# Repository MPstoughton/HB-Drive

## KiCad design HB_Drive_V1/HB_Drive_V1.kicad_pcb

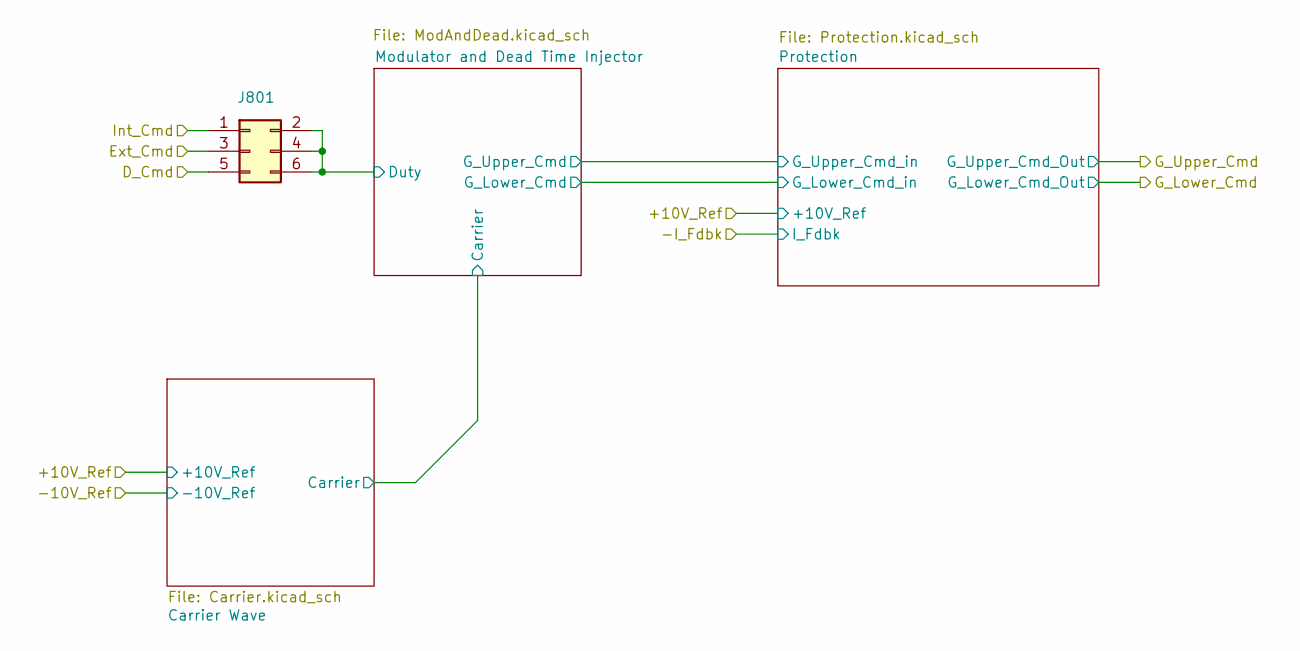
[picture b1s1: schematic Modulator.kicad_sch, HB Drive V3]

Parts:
J801: Conn_02x03_Odd_Even; PinHeader_2x03_P2.54mm_Vertical

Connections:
/Ext_Cmd: J801.3; also elsewhere on the board
/Inner Current Regulator/D_Cmd: J801.5; also elsewhere on the board
/Int_Cmd: J801.1; also elsewhere on the board
/Modulator and Protection/Modulator and Dead Time Injector/Duty: J801.2, J801.4, J801.6; also elsewhere on the board

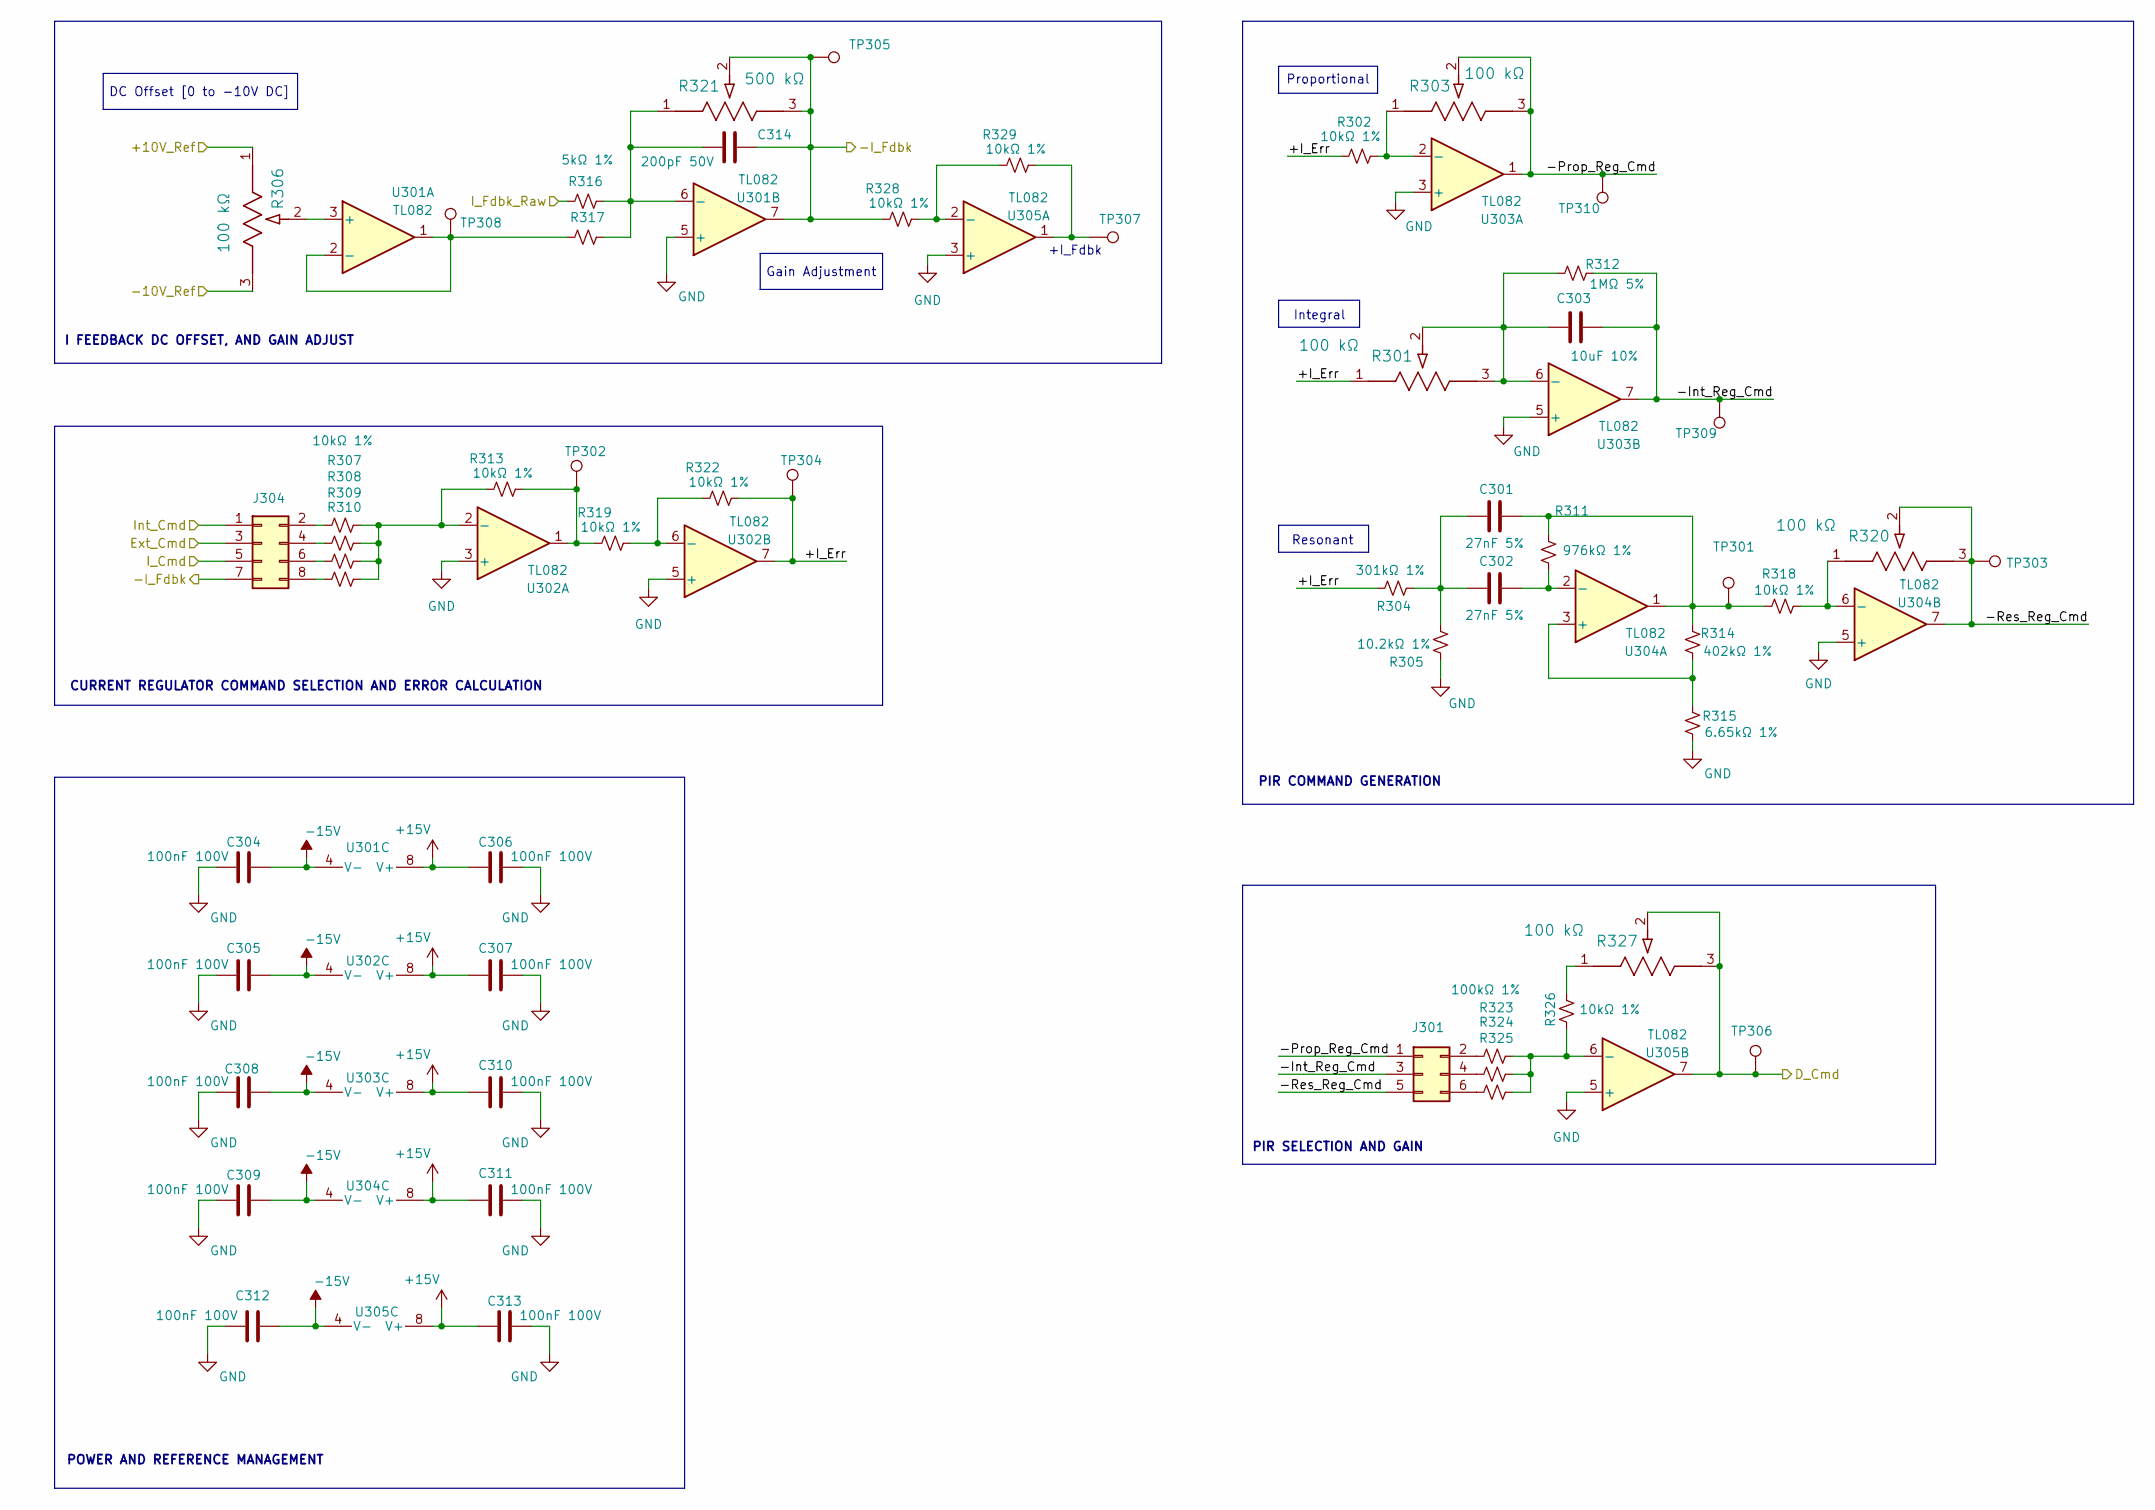
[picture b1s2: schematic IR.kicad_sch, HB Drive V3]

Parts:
C301, C302: 27nF 5%; C_0603_1608Metric
C303: 10uF 10%; C_0603_1608Metric
C304, C305, C306, C307, C308, C309, C310, C311, C312, C313: 100nF 100V; C_0603_1608Metric
C314: 200pF 50V; C_0603_1608Metric
J301: Conn_02x03_Odd_Even; PinHeader_2x03_P2.54mm_Vertical
J304: Conn_02x04_Odd_Even; PinHeader_2x04_P2.54mm_Vertical
R301, R303, R306, R320, R327: 100 kΩ; POT_PV36W_BRN
R302, R307, R308, R309, R310, R313, R318, R319, R322, R326, R328, R329: 10kΩ 1%; R_0603_1608Metric_Pad0.98x0.95mm_HandSolder
R304: 301kΩ 1%; R_0603_1608Metric_Pad0.98x0.95mm_HandSolder
R305: 10.2kΩ 1%; R_0603_1608Metric_Pad0.98x0.95mm_HandSolder
R311: 976kΩ 1%; R_0603_1608Metric_Pad0.98x0.95mm_HandSolder
R312: 1MΩ 5%; R_0603_1608Metric_Pad0.98x0.95mm_HandSolder
R314: 402kΩ 1%; R_0603_1608Metric_Pad0.98x0.95mm_HandSolder
R315: 6.65kΩ 1%; R_0603_1608Metric_Pad0.98x0.95mm_HandSolder
R316, R317: 5kΩ 1%; R_0603_1608Metric_Pad0.98x0.95mm_HandSolder
R321: 500 kΩ; POT_PV36W_BRN
R323, R324, R325: 100kΩ 1%; R_0603_1608Metric_Pad0.98x0.95mm_HandSolder
TP301, TP302, TP303, TP304, TP305, TP306, TP307, TP308, TP309, TP310: TestPoint; TestPoint_Loop_D2.60mm_Drill1.6mm_Beaded
U301, U302, U303, U304, U305: TL082; SOIC-8_3.9x4.9mm_P1.27mm

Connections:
+15V: C306.2, C307.2, C310.2, C311.2, C313.2, U301.8 (V+), U302.8 (V+), U303.8 (V+), U304.8 (V+), U305.8 (V+); also elsewhere on the board
-15V: C304.1, C305.1, C308.1, C309.1, C312.1, U301.4 (V-), U302.4 (V-), U303.4 (V-), U304.4 (V-), U305.4 (V-); also elsewhere on the board
/+10V_Ref: R306.1; also elsewhere on the board
/-10V_Ref: R306.3; also elsewhere on the board
/Ext_Cmd: J304.3; also elsewhere on the board
/I_Fdbk_Raw: R316.2; also elsewhere on the board
/Inner Current Regulator/+I_Err: R301.1, R302.1, R304.2, R322.1, TP304.1 (1_1), U302.7
/Inner Current Regulator/-I_Fdbk: C314.1, J304.7, R321.2, R321.3, R328.2, TP305.1 (1_1), U301.7; also elsewhere on the board
/Inner Current Regulator/-Int_Reg_Cmd: C303.1, J301.3, R312.2, TP309.1 (1_1), U303.7
/Inner Current Regulator/-Prop_Reg_Cmd: J301.1, R303.2, R303.3, TP310.1 (1_1), U303.1
/Inner Current Regulator/-Res_Reg_Cmd: J301.5, R320.2, R320.3, TP303.1 (1_1), U304.7
/Inner Current Regulator/D_Cmd: R327.2, R327.3, TP306.1 (1_1), U305.7; also elsewhere on the board
/Inner Current Regulator/I_Cmd: J304.5; also elsewhere on the board
/Int_Cmd: J304.1; also elsewhere on the board
GND: C304.2, C305.2, C306.1, C307.1, C308.2, C309.2, C310.1, C311.1, C312.2, C313.1, R305.2, R315.1, U301.5 (+), U302.3 (+), U302.5 (+), U303.3 (+), U303.5 (+), U304.5 (+), U305.3 (+), U305.5 (+); also elsewhere on the board
unnamed: C301.1, R311.2, R314.2, R318.2, TP301.1 (1_1), U304.1
unnamed: C301.2, C302.2, R304.1, R305.1
unnamed: J301.2, R323.2
unnamed: J301.4, R324.2
unnamed: J301.6, R325.2
unnamed: J304.2, R307.2
unnamed: J304.4, R308.1
unnamed: J304.6, R309.1
unnamed: J304.8, R310.1
unnamed: R313.1, R319.2, TP302.1 (1_1), U302.1
unnamed: R326.2, R327.1
unnamed: R329.1, TP307.1 (1_1), U305.1
unnamed: R306.2, U301.3 (+)
unnamed: R317.2, TP308.1 (1_1), U301.1, U301.2 (-)
unnamed: C314.2, R316.1, R317.1, R321.1, U301.6 (-)
unnamed: R307.1, R308.2, R309.2, R310.2, R313.2, U302.2 (-)
unnamed: R319.1, R322.2, U302.6 (-)
unnamed: R302.2, R303.1, U303.2 (-)
unnamed: C303.2, R301.2, R301.3, R312.1, U303.6 (-)
unnamed: R314.1, R315.2, U304.3 (+)
unnamed: C302.1, R311.1, U304.2 (-)
unnamed: R318.1, R320.1, U304.6 (-)
unnamed: R328.1, R329.2, U305.2 (-)
unnamed: R323.1, R324.1, R325.1, R326.1, U305.6 (-)

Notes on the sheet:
DC Offset [0 to -10V DC]
CURRENT REGULATOR COMMAND SELECTION AND ERROR CALCULATION
Proportional
Resonant
PIR COMMAND GENERATION
I FEEDBACK DC OFFSET, AND GAIN ADJUST
+I_Fdbk
POWER AND REFERENCE MANAGEMENT
PIR SELECTION AND GAIN
Integral
Gain Adjustment

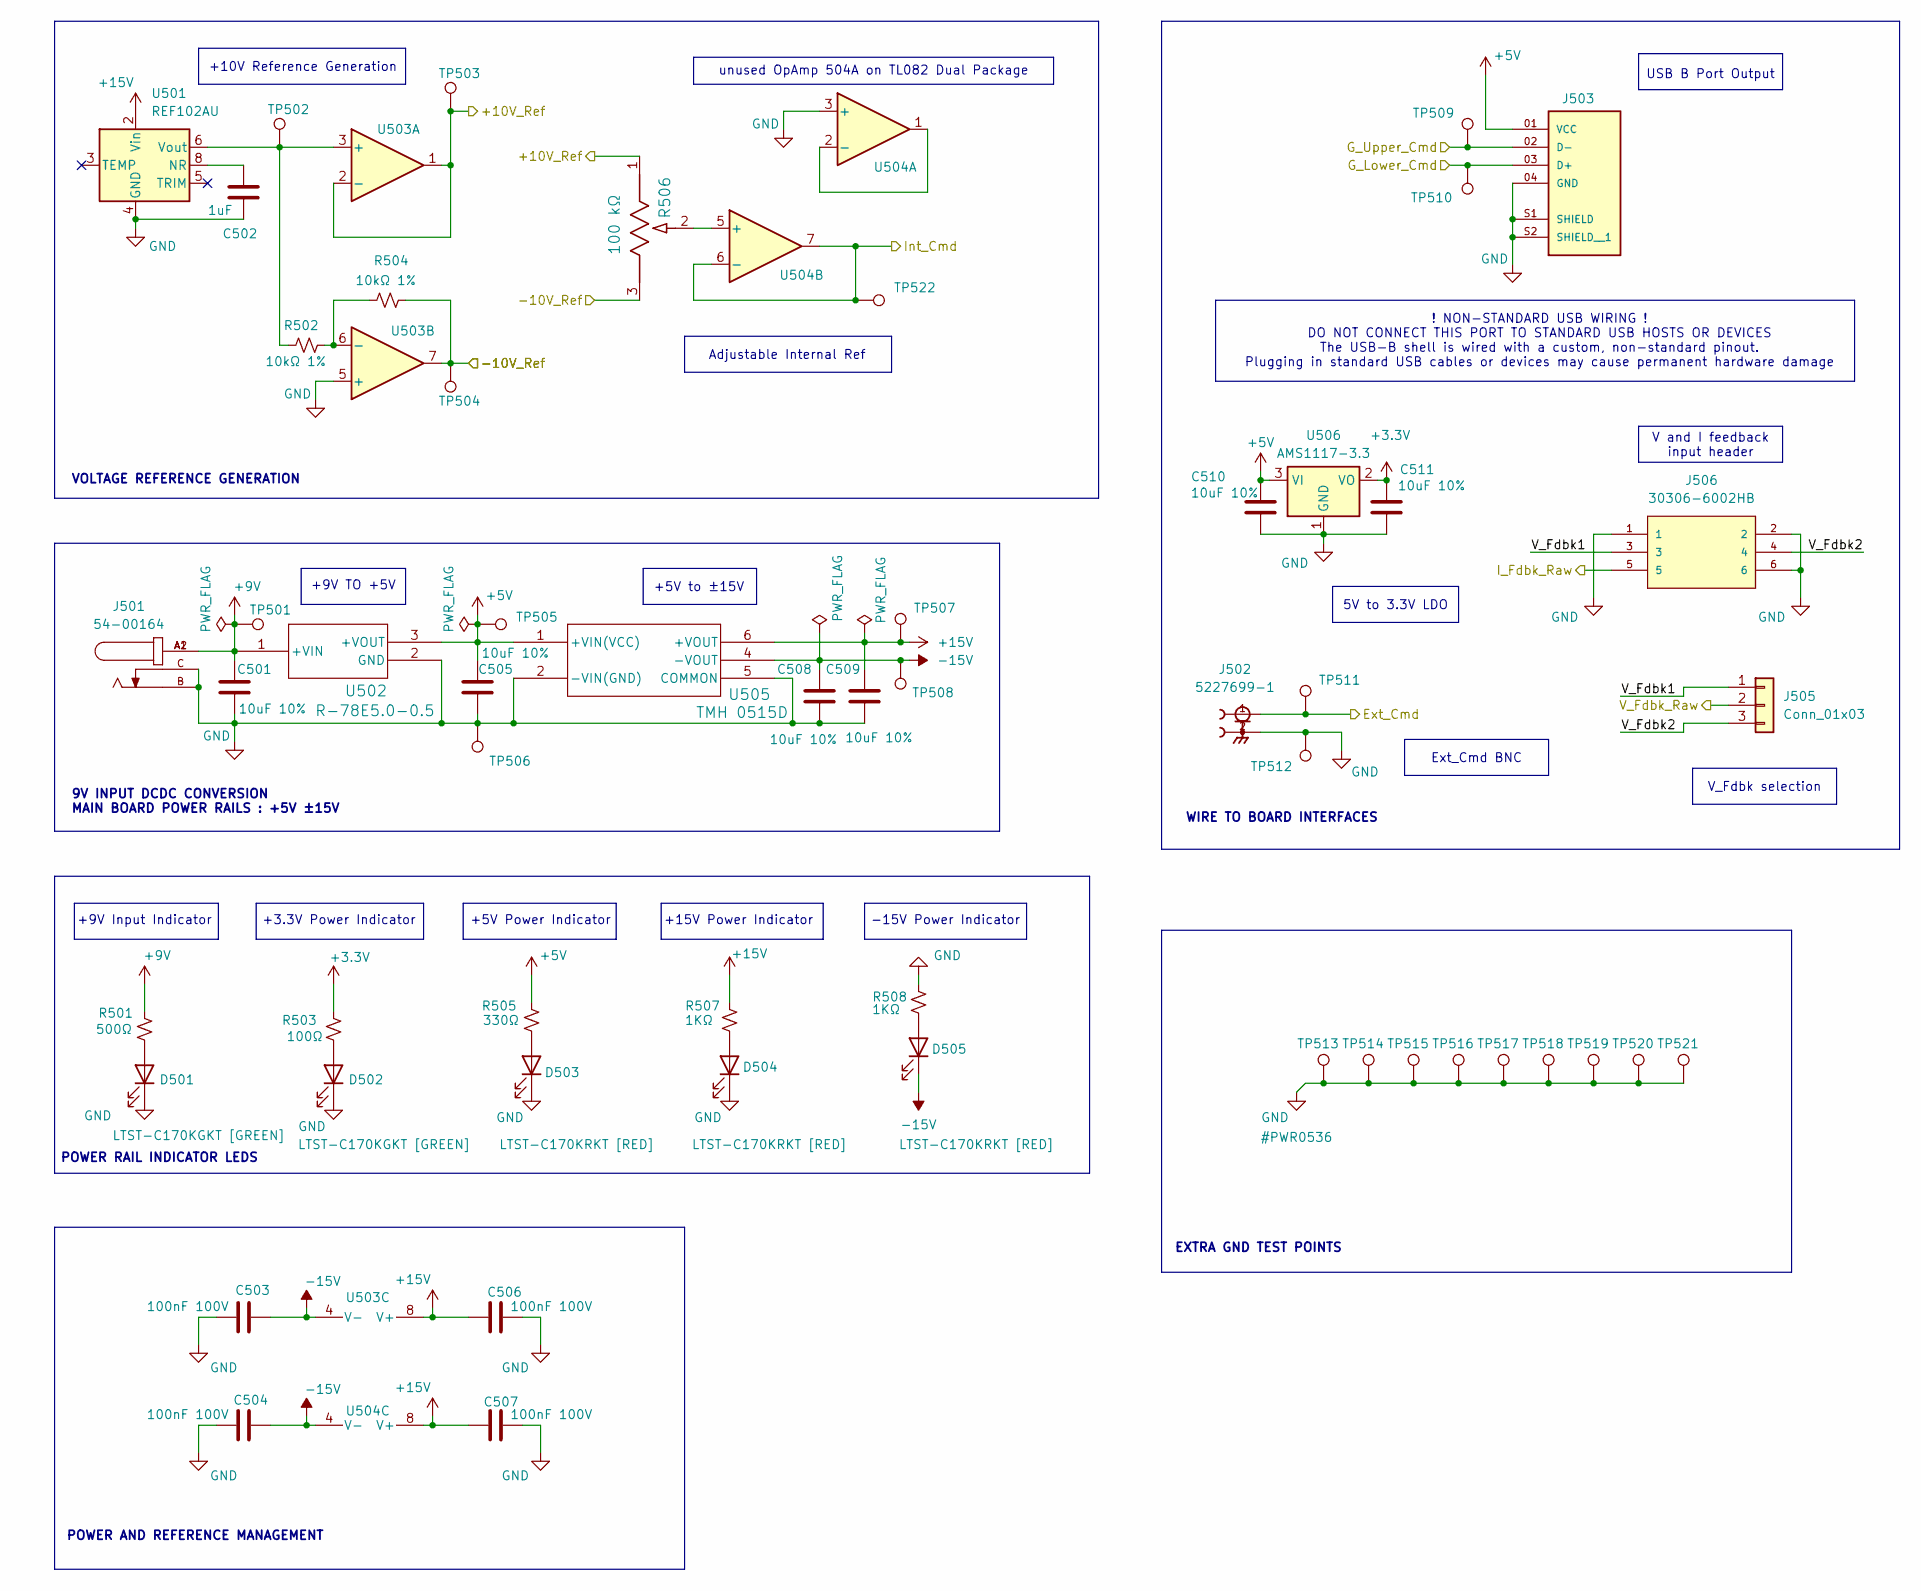
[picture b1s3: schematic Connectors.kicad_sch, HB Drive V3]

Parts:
C501, C505, C508, C509, C510, C511: 10uF 10%; C_0603_1608Metric
C502: 1uF; C_0603_1608Metric
C503, C504, C506, C507: 100nF 100V; C_0603_1608Metric
D501, D502: LTST-C170KGKT [GREEN]; LED_0805_2012Metric_Pad1.15x1.40mm_HandSolder
D503, D504, D505: LTST-C170KRKT [RED]; LED_0805_2012Metric_Pad1.15x1.40mm_HandSolder
J501: 54-00164; TENSILITY_54-00164; PARTREV A
J502: 5227699-1; TE_5227699-1; PARTREV A; DigiKey_Part_Number A33798-ND
J503: USB-B-S-X-X-VT; USB-B-S-VT; PARTREV Q
J505: Conn_01x03; PinHeader_1x03_P2.54mm_Vertical
J506: 30306-6002HB
R501: 500Ω; R_0603_1608Metric_Pad0.98x0.95mm_HandSolder
R502, R504: 10kΩ 1%; R_0603_1608Metric_Pad0.98x0.95mm_HandSolder
R503: 100Ω; R_0603_1608Metric_Pad0.98x0.95mm_HandSolder
R505: 330Ω; R_0603_1608Metric_Pad0.98x0.95mm_HandSolder
R506: 100 kΩ; POT_PV36W_BRN
R507, R508: 1KΩ; R_0603_1608Metric_Pad0.98x0.95mm_HandSolder
TP501, TP502, TP503, TP504, TP505, TP506, TP507, TP508, TP509, TP510, TP511, TP512, TP513, TP514, TP515, TP516, TP517, TP518, TP519, TP520, TP521, TP522: TestPoint; TestPoint_Loop_D2.60mm_Drill1.6mm_Beaded
U501: REF102AU; SOIC-8_3.9x4.9mm_P1.27mm
U502: R-78E5.0-0.5; R_78E_0.5_RCP
U503, U504: TL082; SOIC-8_3.9x4.9mm_P1.27mm
U505: TMH 0515D; TMH DUAL_TRP
U506: AMS1117-3.3; SOT-223-3_TabPin2

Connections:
+3.3V: C511.1, R503.2, U506.2 (VO); also elsewhere on the board
+5V: C505.1, C510.1, J503.01 (VCC), R505.2, TP505.1 (1_1), U502.3 (+VOUT), U505.1 (+VIN(VCC)), U506.3 (VI); also elsewhere on the board
+9V: C501.1, J501.A1, J501.A2, R501.2, TP501.1 (1_1), U502.1 (+VIN)
+15V: C506.2, C507.2, C509.1, R507.2, TP507.1 (1_1), U501.2 (Vin), U503.8 (V+), U504.8 (V+), U505.6 (+VOUT); also elsewhere on the board
-15V: C503.1, C504.1, C508.1, D505.1 (K), TP508.1 (1_1), U503.4 (V-), U504.4 (V-), U505.4 (-VOUT); also elsewhere on the board
/+10V_Ref: R506.1, TP503.1 (1_1), U503.1, U503.2 (-); also elsewhere on the board
/-10V_Ref: R504.2, R506.3, TP504.1 (1_1), U503.7; also elsewhere on the board
/Connectors, Auxillaries, and References/V_Fdbk1: J505.1, J506.3
/Connectors, Auxillaries, and References/V_Fdbk2: J505.3, J506.4
/Ext_Cmd: J502.1, TP511.1 (1_1); also elsewhere on the board
/G_Lower_Cmd: J503.03 (D+), TP510.1 (1_1); also elsewhere on the board
/G_Upper_Cmd: J503.02 (D-), TP509.1 (1_1); also elsewhere on the board
/I_Fdbk_Raw: J506.5; also elsewhere on the board
/Int_Cmd: TP522.1 (1_1), U504.6 (-), U504.7; also elsewhere on the board
/V_Fdbk_Raw: J505.2; also elsewhere on the board
GND: C501.2, C502.1, C503.2, C504.2, C505.2, C506.1, C507.1, C508.2, C509.2, C510.2, C511.2, D501.1 (K), D502.1 (K), D503.1 (K), D504.1 (K), J501.B, J501.C, J502.2, J502.3, J502.4, J502.5, J503.04 (GND), J503.S1 (SHIELD), J503.S2 (SHIELD__1), J506.1, J506.2, J506.6, R508.2, TP506.1 (1_1), TP512.1 (1_1), TP513.1 (1_1), TP514.1 (1_1), TP515.1 (1_1), TP516.1 (1_1), TP517.1 (1_1), TP518.1 (1_1), TP519.1 (1_1), TP520.1 (1_1), TP521.1 (1_1), U501.4 (GND), U502.2 (GND), U503.5 (+), U504.3 (+), U505.2 (-VIN(GND)), U505.5 (COMMON), U506.1 (GND); also elsewhere on the board
unnamed: D501.2 (A), R501.1
unnamed: D502.2 (A), R503.1
unnamed: D503.2 (A), R505.1
unnamed: D504.2 (A), R507.1
unnamed: D505.2 (A), R508.1
unnamed: C502.2, U501.8 (NR)
unnamed: R502.1, TP502.1 (1_1), U501.6 (Vout), U503.3 (+)
unnamed: R502.2, R504.1, U503.6 (-)
unnamed: U504.1, U504.2 (-)
unnamed: R506.2, U504.5 (+)

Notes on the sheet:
POWER RAIL INDICATOR LEDS
Adjustable Internal Ref
unused OpAmp 504A on TL082 Dual Package
EXTRA GND TEST POINTS
+3.3V Power Indicator
+5V to ±15V
+10V Reference Generation
+9V TO +5V
POWER AND REFERENCE MANAGEMENT
+9V Input Indicator
9V INPUT DCDC CONVERSION MAIN BOARD POWER RAILS : +5V ±15V
VOLTAGE REFERENCE GENERATION
+15V Power Indicator
V_Fdbk selection
! NON-STANDARD USB WIRING ! DO NOT CONNECT THIS PORT TO STANDARD USB HOSTS OR DEVICES The USB-B shell is wired with a custom, non-standard pinout. Plugging in standard USB cables or devices may cause permanent hardware damage
+5V Power Indicator
WIRE TO BOARD INTERFACES
USB B Port Output
-15V Power Indicator
V and I feedback input header
Ext_Cmd BNC
5V to 3.3V LDO

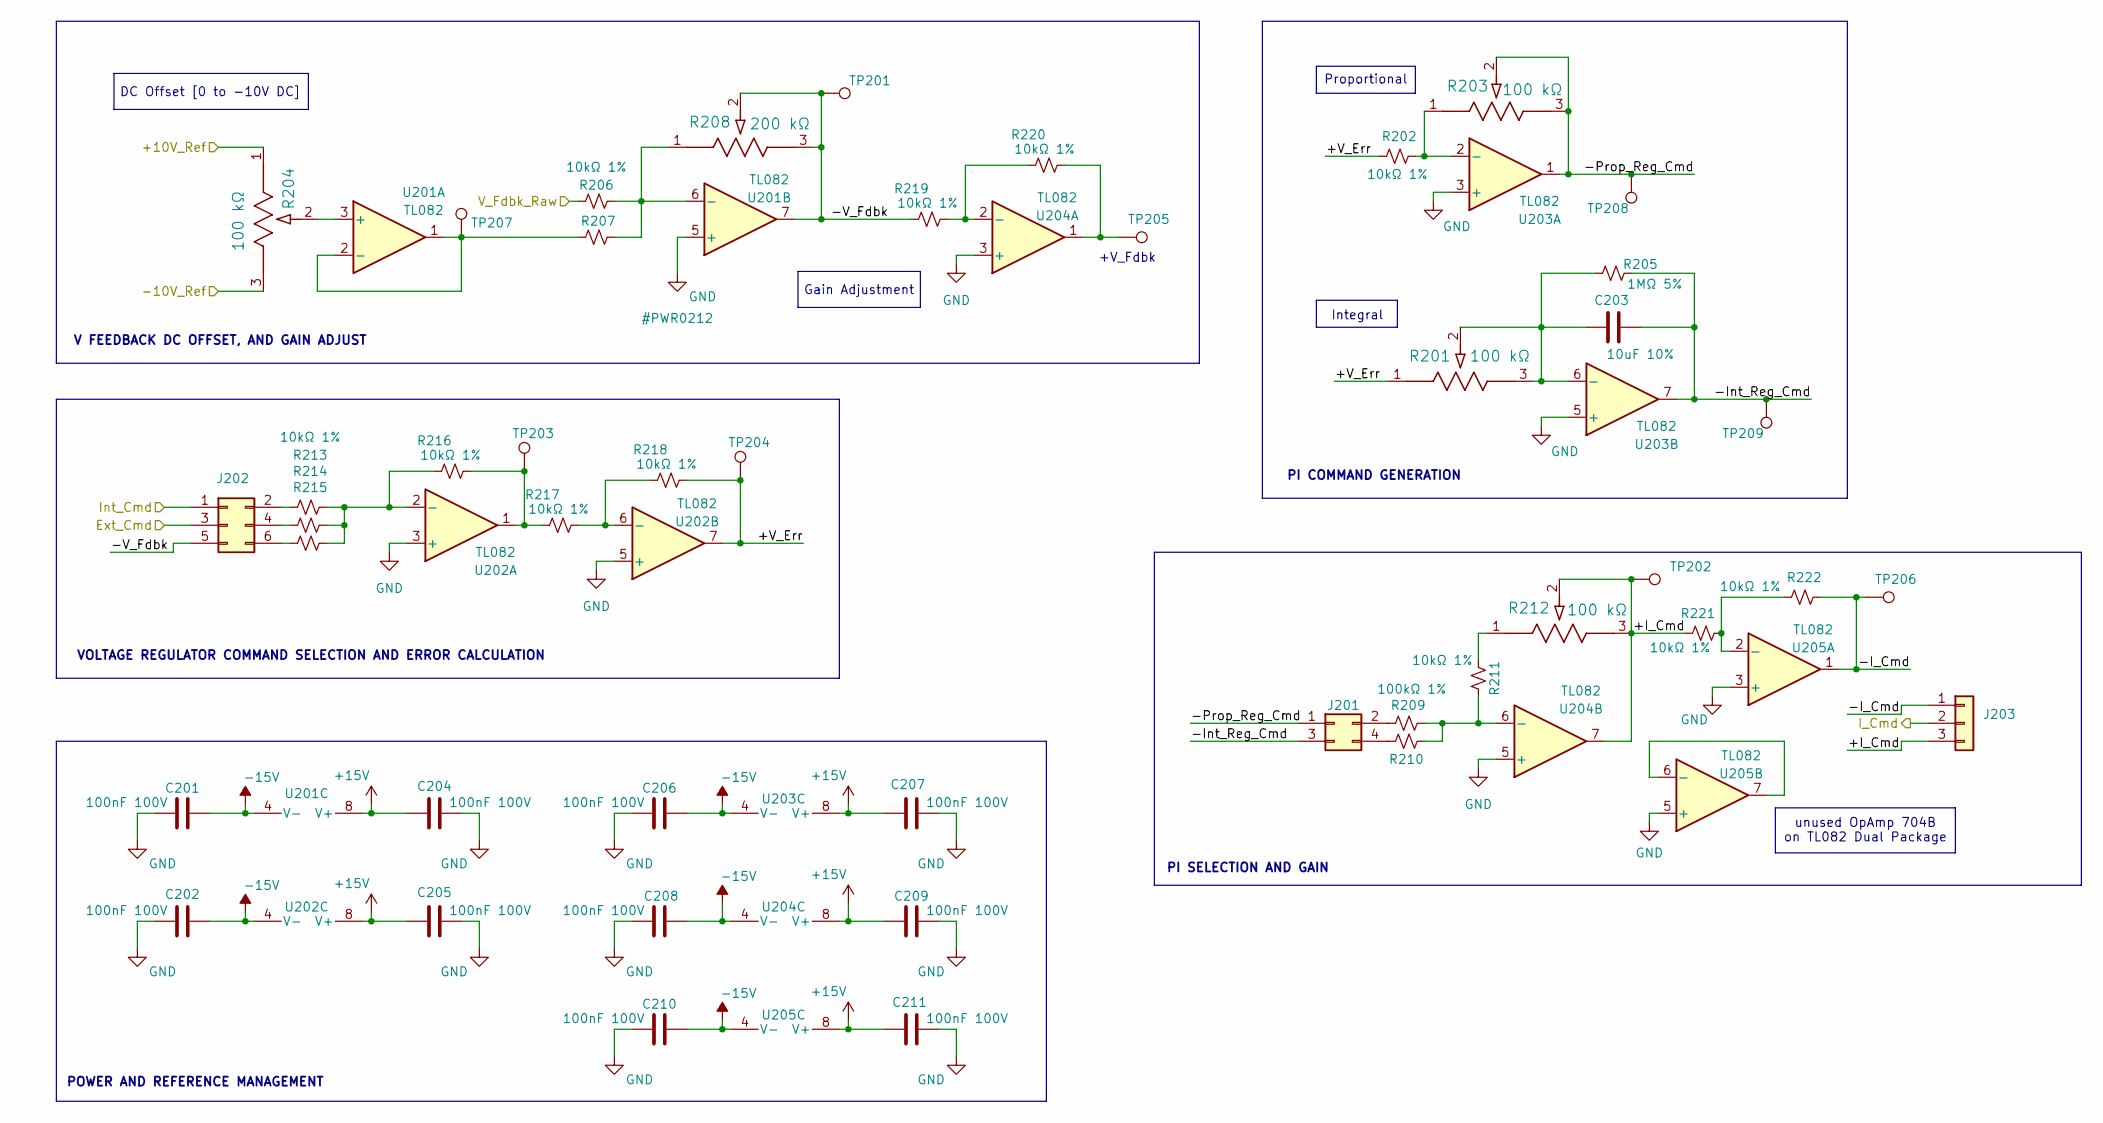
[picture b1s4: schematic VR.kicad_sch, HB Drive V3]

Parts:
C201, C202, C204, C205, C206, C207, C208, C209, C210, C211: 100nF 100V; C_0603_1608Metric
C203: 10uF 10%; C_0603_1608Metric
J201: Conn_02x02_Odd_Even; PinHeader_2x02_P2.54mm_Vertical
J202: Conn_02x03_Odd_Even; PinHeader_2x03_P2.54mm_Vertical
J203: Conn_01x03; PinHeader_1x03_P2.54mm_Vertical
R201, R203, R204, R212: 100 kΩ; POT_PV36W_BRN
R202, R206, R207, R210, R211, R213, R214, R215, R216, R217, R218, R219, R220, R221, R222: 10kΩ 1%; R_0603_1608Metric_Pad0.98x0.95mm_HandSolder
R205: 1MΩ 5%; R_0603_1608Metric_Pad0.98x0.95mm_HandSolder
R208: 200 kΩ; POT_PV36W_BRN
R209: 100kΩ 1%; R_0603_1608Metric_Pad0.98x0.95mm_HandSolder
TP201, TP202, TP203, TP204, TP205, TP206, TP207, TP208, TP209: TestPoint; TestPoint_Loop_D2.60mm_Drill1.6mm_Beaded
U201, U202, U203, U204, U205: TL082; SOIC-8_3.9x4.9mm_P1.27mm

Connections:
+15V: C204.2, C205.2, C207.2, C209.2, C211.2, U201.8 (V+), U202.8 (V+), U203.8 (V+), U204.8 (V+), U205.8 (V+); also elsewhere on the board
-15V: C201.1, C202.1, C206.1, C208.1, C210.1, U201.4 (V-), U202.4 (V-), U203.4 (V-), U204.4 (V-), U205.4 (V-); also elsewhere on the board
/+10V_Ref: R204.1; also elsewhere on the board
/-10V_Ref: R204.3; also elsewhere on the board
/Ext_Cmd: J202.3; also elsewhere on the board
/Inner Current Regulator/I_Cmd: J203.2; also elsewhere on the board
/Int_Cmd: J202.1; also elsewhere on the board
/Outer Voltage Regulator/+I_Cmd: J203.3, R212.2, R212.3, R221.2, TP202.1 (1_1), U204.7
/Outer Voltage Regulator/+V_Err: R201.1, R202.1, R218.1, TP204.1 (1_1), U202.7
/Outer Voltage Regulator/-I_Cmd: J203.1, R222.1, TP206.1 (1_1), U205.1
/Outer Voltage Regulator/-Int_Reg_Cmd: C203.1, J201.3, R205.2, TP209.1 (1_1), U203.7
/Outer Voltage Regulator/-Prop_Reg_Cmd: J201.1, R203.2, R203.3, TP208.1 (1_1), U203.1
/Outer Voltage Regulator/-V_Fdbk: J202.5, R208.2, R208.3, R219.2, TP201.1 (1_1), U201.7
/V_Fdbk_Raw: R206.2; also elsewhere on the board
GND: C201.2, C202.2, C204.1, C205.1, C206.2, C207.1, C208.2, C209.1, C210.2, C211.1, U201.5 (+), U202.3 (+), U202.5 (+), U203.3 (+), U203.5 (+), U204.3 (+), U204.5 (+), U205.3 (+), U205.5 (+); also elsewhere on the board
unnamed: J201.2, R209.2
unnamed: J201.4, R210.1
unnamed: J202.2, R213.2
unnamed: J202.4, R214.1
unnamed: J202.6, R215.1
unnamed: R211.2, R212.1
unnamed: R216.1, R217.2, TP203.1 (1_1), U202.1
unnamed: R220.1, TP205.1 (1_1), U204.1
unnamed: R204.2, U201.3 (+)
unnamed: R207.2, TP207.1 (1_1), U201.1, U201.2 (-)
unnamed: R206.1, R207.1, R208.1, U201.6 (-)
unnamed: R213.1, R214.2, R215.2, R216.2, U202.2 (-)
unnamed: R217.1, R218.2, U202.6 (-)
unnamed: R202.2, R203.1, U203.2 (-)
unnamed: C203.2, R201.2, R201.3, R205.1, U203.6 (-)
unnamed: R219.1, R220.2, U204.2 (-)
unnamed: R209.1, R210.2, R211.1, U204.6 (-)
unnamed: R221.1, R222.2, U205.2 (-)
unnamed: U205.6 (-), U205.7

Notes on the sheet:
PI SELECTION AND GAIN
Proportional
Gain Adjustment
DC Offset [0 to -10V DC]
unused OpAmp 704B on TL082 Dual Package
VOLTAGE REGULATOR COMMAND SELECTION AND ERROR CALCULATION
V FEEDBACK DC OFFSET, AND GAIN ADJUST
Integral
+V_Fdbk
PI COMMAND GENERATION
POWER AND REFERENCE MANAGEMENT

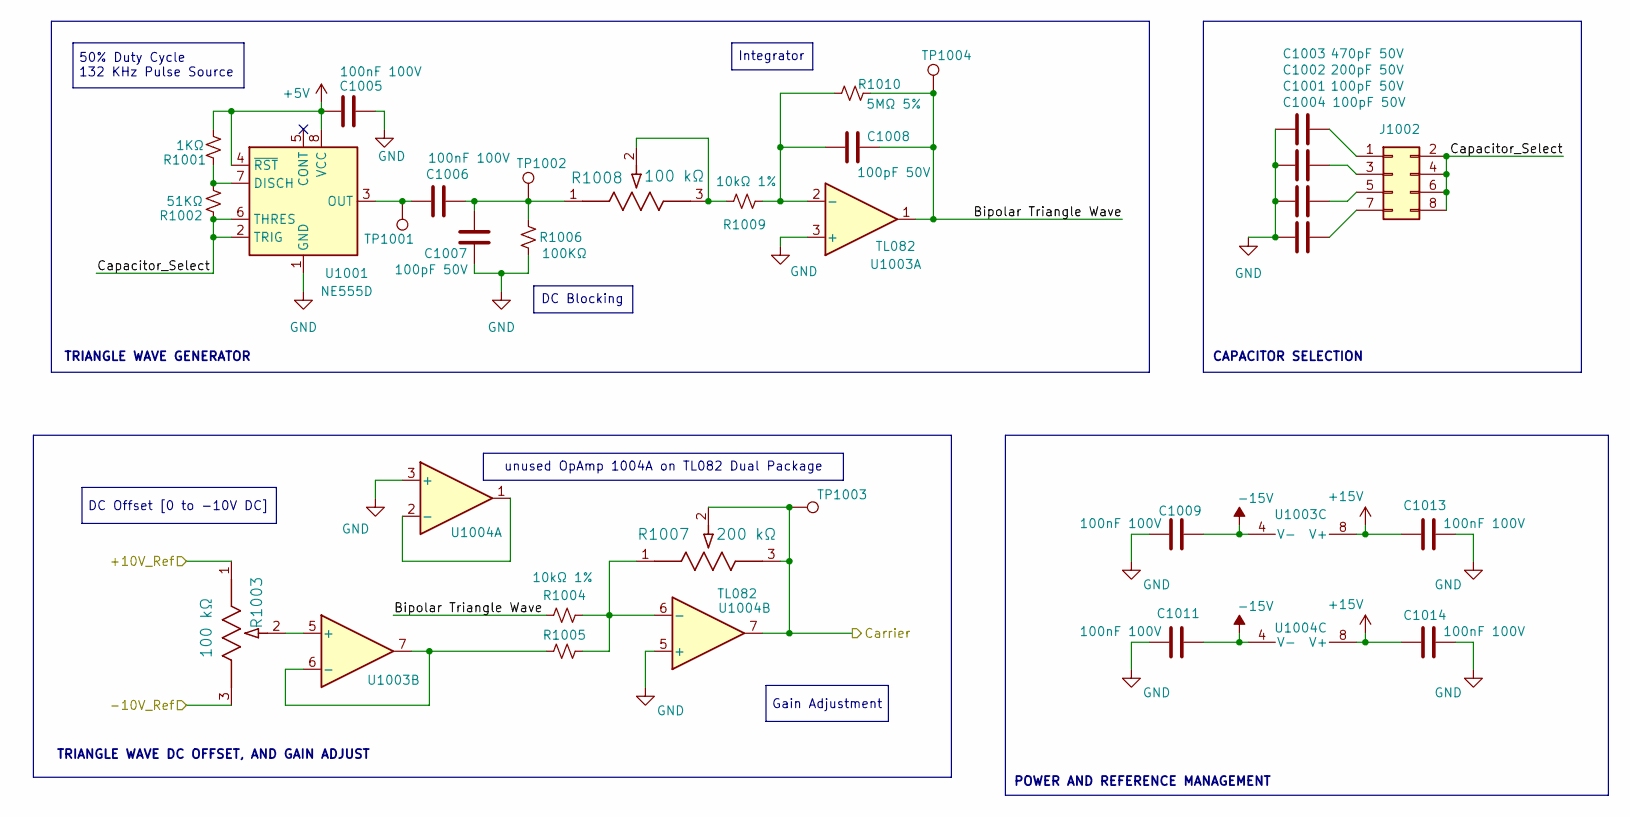
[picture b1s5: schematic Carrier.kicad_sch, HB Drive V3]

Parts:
C1001, C1004, C1007, C1008: 100pF 50V; C_0603_1608Metric
C1002: 200pF 50V; C_0603_1608Metric
C1003: 470pF 50V; C_0603_1608Metric
C1005, C1006, C1009, C1011, C1013, C1014: 100nF 100V; C_0603_1608Metric
J1002: Conn_02x04_Odd_Even; PinHeader_2x04_P2.54mm_Vertical
R1001: 1KΩ; R_0603_1608Metric_Pad0.98x0.95mm_HandSolder
R1002: 51KΩ; R_0603_1608Metric_Pad0.98x0.95mm_HandSolder
R1003, R1008: 100 kΩ; POT_PV36W_BRN
R1004, R1005, R1009: 10kΩ 1%; R_0603_1608Metric_Pad0.98x0.95mm_HandSolder
R1006: 100KΩ; R_0603_1608Metric_Pad0.98x0.95mm_HandSolder
R1007: 200 kΩ; POT_PV36W_BRN
R1010: 5MΩ 5%; R_0603_1608Metric_Pad0.98x0.95mm_HandSolder
TP1001, TP1002, TP1003, TP1004: TestPoint; TestPoint_Loop_D2.60mm_Drill1.6mm_Beaded
U1001: NE555D; SOIC-8_3.9x4.9mm_P1.27mm
U1003, U1004: TL082; SOIC-8_3.9x4.9mm_P1.27mm

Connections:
+5V: C1005.2, R1001.1, U1001.4 (~RST), U1001.8 (VCC); also elsewhere on the board
+15V: C1013.2, C1014.2, U1003.8 (V+), U1004.8 (V+); also elsewhere on the board
-15V: C1009.1, C1011.1, U1003.4 (V-), U1004.4 (V-); also elsewhere on the board
/+10V_Ref: R1003.1; also elsewhere on the board
/-10V_Ref: R1003.3; also elsewhere on the board
/Modulator and Protection/Carrier Wave/Bipolar Triangle Wave: C1008.2, R1004.2, R1010.2, TP1004.1 (1_1), U1003.1
/Modulator and Protection/Carrier Wave/Capacitor_Select: J1002.2, J1002.4, J1002.6, J1002.8, R1002.2, U1001.2 (TRIG), U1001.6 (THRES)
/Modulator and Protection/Carrier Wave/Carrier: R1007.2, R1007.3, TP1003.1 (1_1), U1004.7; also elsewhere on the board
GND: C1001.2, C1002.2, C1003.2, C1004.2, C1005.1, C1007.2, C1009.2, C1011.2, C1013.1, C1014.1, R1006.2, U1001.1 (GND), U1003.3 (+), U1004.3 (+), U1004.5 (+); also elsewhere on the board
unnamed: C1006.1, C1007.1, R1006.1, R1008.1, TP1002.1 (1_1)
unnamed: C1003.1, J1002.1
unnamed: C1002.1, J1002.3
unnamed: C1001.1, J1002.5
unnamed: C1004.1, J1002.7
unnamed: R1008.2, R1008.3, R1009.1
unnamed: R1001.2, R1002.1, U1001.7 (DISCH)
unnamed: C1006.2, TP1001.1 (1_1), U1001.3 (OUT)
unnamed: C1008.1, R1009.2, R1010.1, U1003.2 (-)
unnamed: R1003.2, U1003.5 (+)
unnamed: R1005.2, U1003.6 (-), U1003.7
unnamed: U1004.1, U1004.2 (-)
unnamed: R1004.1, R1005.1, R1007.1, U1004.6 (-)

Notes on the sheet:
CAPACITOR SELECTION
TRIANGLE WAVE GENERATOR
DC Blocking
unused OpAmp 1004A on TL082 Dual Package
TRIANGLE WAVE DC OFFSET, AND GAIN ADJUST
50% Duty Cycle 132 KHz Pulse Source
DC Offset [0 to -10V DC]
Gain Adjustment
POWER AND REFERENCE MANAGEMENT
Integrator

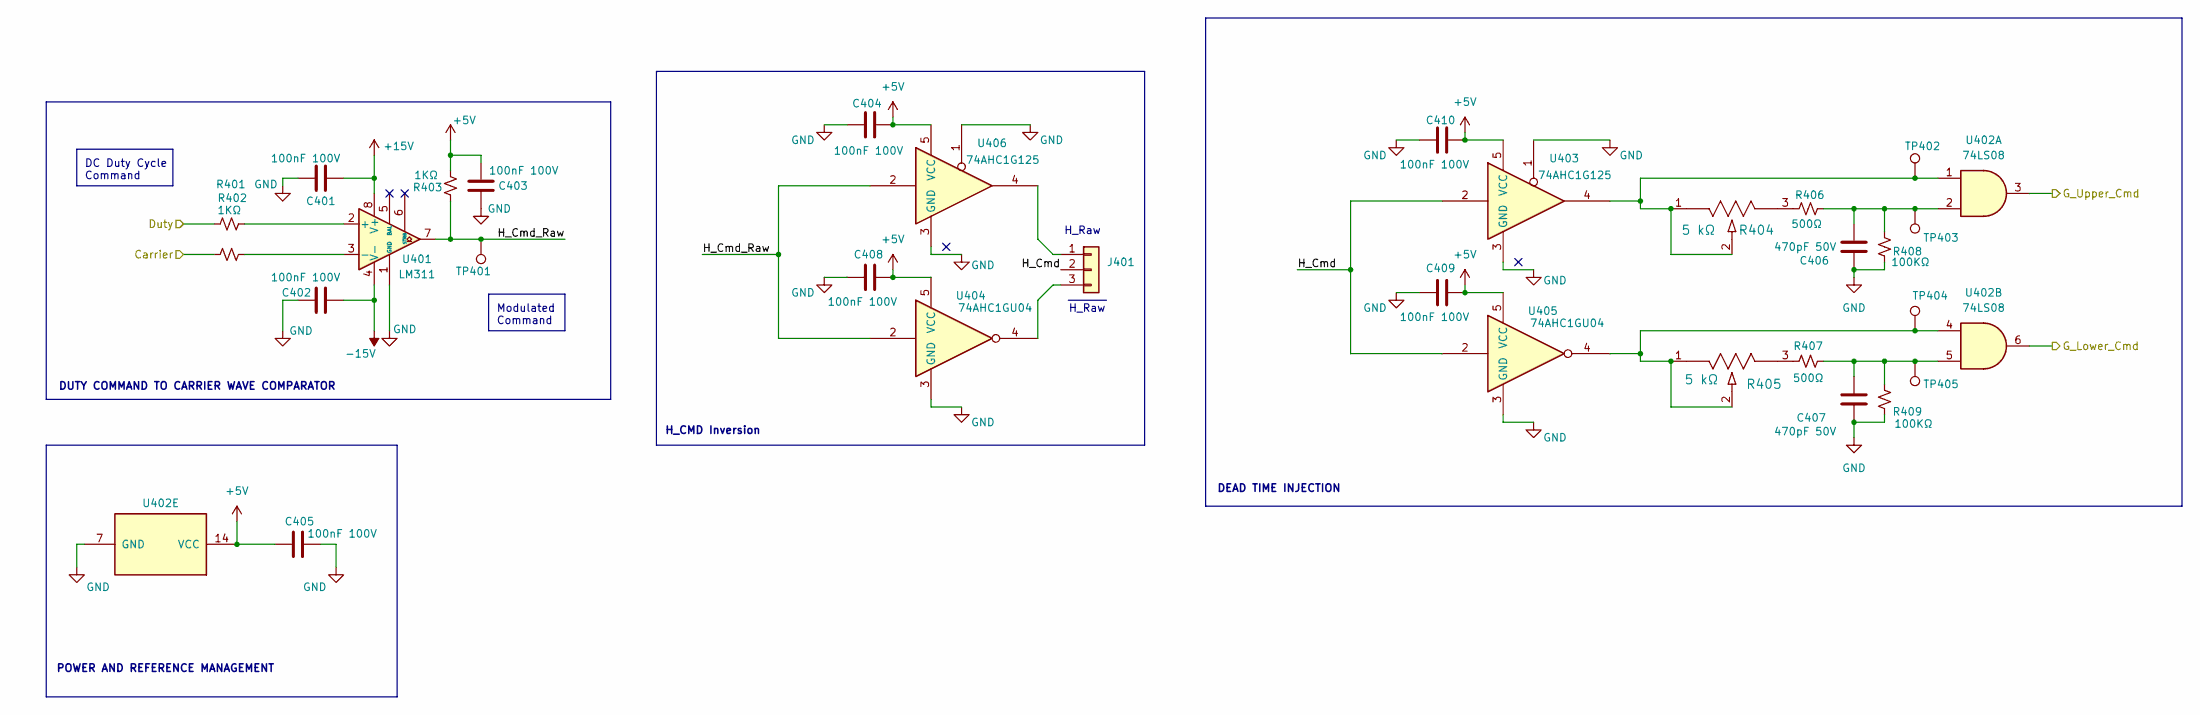
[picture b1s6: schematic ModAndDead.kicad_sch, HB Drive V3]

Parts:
C401, C402, C403, C404, C405, C408, C409, C410: 100nF 100V; C_0603_1608Metric
C406, C407: 470pF 50V; C_0603_1608Metric
J401: Conn_01x03; PinHeader_1x03_P2.54mm_Vertical
R401, R402, R403: 1KΩ; R_0603_1608Metric_Pad0.98x0.95mm_HandSolder
R404, R405: 5 kΩ; POT_PV36W_BRN
R406, R407: 500Ω; R_0603_1608Metric_Pad0.98x0.95mm_HandSolder
R408, R409: 100KΩ; R_0603_1608Metric_Pad0.98x0.95mm_HandSolder
TP401, TP402, TP403, TP404, TP405: TestPoint; TestPoint_Loop_D2.60mm_Drill1.6mm_Beaded
U401: LM311; SOIC-8_3.9x4.9mm_P1.27mm
U402: 74LS08; SOIC-14_3.9x8.7mm_P1.27mm
U403, U406: 74AHC1G125; SOT-23-5
U404, U405: 74AHC1GU04; SOT-23-5

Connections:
+5V: C403.2, C404.1, C405.2, C408.1, C409.1, C410.1, R403.2, U402.14 (VCC), U403.5 (VCC), U404.5 (VCC), U405.5 (VCC), U406.5 (VCC); also elsewhere on the board
+15V: C401.1, U401.8 (V+); also elsewhere on the board
-15V: C402.1, U401.4 (V-); also elsewhere on the board
/Modulator and Protection/Carrier Wave/Carrier: R402.1; also elsewhere on the board
/Modulator and Protection/Modulator and Dead Time Injector/Duty: R401.1; also elsewhere on the board
/Modulator and Protection/Modulator and Dead Time Injector/G_Lower_Cmd: U402.6; also elsewhere on the board
/Modulator and Protection/Modulator and Dead Time Injector/G_Upper_Cmd: U402.3; also elsewhere on the board
/Modulator and Protection/Modulator and Dead Time Injector/H_Cmd: J401.2, U403.2, U405.2
/Modulator and Protection/Modulator and Dead Time Injector/H_Cmd_Raw: R403.1, TP401.1 (1_1), U401.7, U404.2, U406.2
GND: C401.2, C402.2, C403.1, C404.2, C405.1, C406.2, C407.2, C408.2, C409.2, C410.2, R408.2, R409.2, U401.1 (GND), U402.7 (GND), U403.1, U403.3 (GND), U404.3 (GND), U405.3 (GND), U406.1, U406.3 (GND); also elsewhere on the board
unnamed: C406.1, R406.2, R408.1, TP403.1 (1_1), U402.2
unnamed: C407.1, R407.2, R409.1, TP405.1 (1_1), U402.5
unnamed: J401.1, U406.4
unnamed: J401.3, U404.4
unnamed: R404.1, R404.2, TP402.1 (1_1), U402.1, U403.4
unnamed: R404.3, R406.1
unnamed: R405.1, R405.2, TP404.1 (1_1), U402.4, U405.4
unnamed: R405.3, R407.1
unnamed: R401.2, U401.2 (+)
unnamed: R402.2, U401.3 (-)

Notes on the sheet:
DUTY COMMAND TO CARRIER WAVE COMPARATOR
DEAD TIME INJECTION
H_Raw
H_CMD Inversion
DC Duty Cycle Command
Modulated Command
POWER AND REFERENCE MANAGEMENT
